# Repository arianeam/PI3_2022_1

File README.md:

# PI3_2022_1: Vaso Inteligente

## Estrutura das pastas do projeto:

* app: Nesta pasta está disponível para download o aplicativo de celular.
* banco_de_dados: nesta pasta está disponível o arquivo JSON do Firebase Realtime Database utilizado, que pode ser importado para visualização e uso no Realtime Database.
* firmware: disponível o firmware para esp32 do projeto.
* hardware: disponível o projeto desenvolvido no kicad para a placa.
* imagens PI3: imagens utilizadas nas animações do display, a imagem do mascote do aplicativo, imagens utilizadas nesta documentação, e imagens utilizadas nos testes do display.

# Objetivo
O objetivo deste projeto é implementar um vaso inteligente baseado em Internet das Coisas, que irá monitorar os parâmetros de umidade do solo, luminosidade e temperatura de uma planta, e a partir destes parâmetros avaliar o estado da planta, com base em um banco de dados que contenha informações de espécies de plantas, ou dados personalizados pelo usuário. Detectando o estado da planta, será gerada uma expressão facial em um display contido no vaso, que representará esse estado, como por exemplo, em caso de falta de água para a planta, o vaso exibiria uma expressão de sede. O usuário poderá selecionar configurar os parâmetros da planta através do aplicativo de celular. Essa configuração poderá ser manual ou automática (selecionando a espécie de planta no aplicativo). 

# Serão monitorados os seguintes itens no vaso/planta:

* Temperatura;
* Umidade do solo;
* Luminosidade

## Luminosidade

A luminosidade será monitorada por faixas, que facilitará a logica para definir o estado da planta e a compreensão por parte do usuário.
Conforme o site "Paisagismo Bauru" em sua postagem ["Dicas de luminosidade para seu jardim", link 4](http://www.paisagismobauru.com.br/curiosidades/curiosidades/), a medição de luminosidade será dividida em três faixas:
* **Sol**:
O dia inteiro com iluminação solar direta. Luminosidade acima de 20.000 lux.

* **Meia Sombra**:
Variando de iluminação de poucas horas na parte da manhã e mais algumas poucas horas de iluminação na parte da tarde. Luminosidade variando de 5.000 a 20.000 lux.

* **Sombra**:
Iluminação indireta. Luminosidade de 2.500 a 5.000 lux.

## Umidade do solo

A umidade do solo também será definida com base em três faixas.
* **Seco**
* **Úmido**
* **Molhado**

# Desenvolvimento

## Sensores

Todos sensores, o display oled, e um dos ESP32 utilizados para o desenvolvimento do PI3, não foram comprados. Ambos integrantes da dupla já possuiam o material em casa. Foi efetuada a compra de mais um ESP32 para um dos integrantes da dupla. E o microprocessador utilizado na placa desenvolvida foi removido de um dos ESP32. Poderiam ter sido utilizados outros sensores de melhor desempenho, porém optou-se por manter o menor custo possível nesta primeira versão do Vaso Inteligente.

A comunicação entre o hardware e o banco de dados utilizado ocorre por meio de Wi-Fi, pois o microprocessador utilizado (ESP32-WROOM-32) possui antena integrada.

**OBS.: Os sensores que utilizam os canais de ADC passam pelo circuito de entradas analógicas antes de chegar aos canais ADC, passando pelos buffers que irão proteger as entradas ADC**

### DHT11: sensor de temperatura e umidade

Datasheet: https://www.mouser.com/datasheet/2/758/DHT11-Technical-Data-Sheet-Translated-Version-1143054.pdf

[O elemento sensor de temperatura é um termistor do tipo NTC e o sensor de Umidade é do modelo HR202, o circuito interno faz a leitura dos sensores e se comunica a um microcontrolador, através de um sinal serial de uma via.](https://www.filipeflop.com/produto/modulo-sensor-de-umidade-e-temperatura-dht11-ky-015/)
O DHT11 foi alimentado com o 3v3 e o GND do ESP32, e o pino de dados foi ligado ao pino D27 do microcontrolador.

## LDR 5mm

Datasheet: https://www.filipeflop.com/img/files/download/Datasheet_LDR.pdf

[O Sensor de Luminosidade LDR (Light Dependent Resistor) é um componente cuja resistência varia de acordo com a intensidade da luz. Quanto mais luz incidir sobre o componente, menor a resistência.](https://www.filipeflop.com/produto/sensor-de-luminosidade-ldr-5mm/). Foi utilizado o canal 5 do ADC1 do ESP32 para receber a tensão do LDR, que em seguida, passa por uma função de leitura do firmware.

Foi necessário realizar a linearização dos valores do LDR para que ele atendesse as faixas de luminosidade exigidas pelo projeto. O método utilizado para realizar a linearização está descrito no seguinte link: https://www.digikey.com/en/maker/projects/design-a-luxmeter-with-an-ldr-and-an-arduino/623aeee0f93e427bb57e02c4592567d1

Passos seguidos para a linearização:

* Um multímetro foi conectado no LDR para monitorar a resistência;
* O luxímetro comercial foi posicionado ao lado do LDR, de forma que a incidência de luz seja a mesma em ambos;
* Em uma planilha foi registrada a resistência do LDR medida pelo multímetro e o valor aferido pelo luxímetro comercial;
* O passo anterior foi repetido para outros níveis de luminosidade, de forma que para cada medida da resistência do LDR houvesse uma medida do luxímetro;
* A partir dos dados registrados na planilha foi gerado um gráfico que pode ser ajustado com base na equação y = m.b. Foi utilizada a expressão fornecida no link informado anteriormente, linearizando o gráfico;

Assim é possível construir a função para leitura do LDR e ajustar os coeficientes.

## Higrômetro HL-69 (YL-69)

Guia (datasheet não encontrado): https://usermanual.wiki/Pdf/instructions.261306374.pdf

[Este Sensor de Umidade do Solo Higrômetro foi feito para detectar as variações de umidade no solo. Ele funciona da seguinte forma: quando o solo está seco, a saída do sensor fica em estado alto e quando úmido, a saída do sensor fica em estado baixo. O limite entre seco e úmido pode ser ajustado através do potenciômetro presente no sensor que regulará a saída digital D0. Contudo, para ter uma resolução melhor, é possível utilizar a saída analógica A0 e conectar a um conversor AD.](https://www.filipeflop.com/produto/sensor-de-umidade-do-solo-higrometro/). Para este projeto foi utilizada a saída analógica A0. O canal 4 do ADC1 do ESP32 é o responsável por receber o valor analógico do higrômetro. A alimentação do sensor foi feita através do 3v3 e GND do ESP32.

## Bateria

Abaixo imagem do circuito do carregador da bateria e função de leitura no firmware. Para medir a tensão da bateria proveniente do circuito do carregador foi utilizado o canal 6 do ADC1 do ESP32.

## Display oled SSD1306 128x64

O display utilizado foi o oled SSD1306 de 128x64. As animações para o display foram desenhadas no software Inkscape, com a área de 128x64px, exportadas para PNG, e em seguida convertida para outra extensão bitmap, a extensão XBM, respeitando a função da biblioteca para display SSD1306 utilizada no firmware, ssd1306_load_xbm. É importante observar quais formatos as funções aceitam quando utilizar bibliotecas de terceiros, caso contrário a imagem será exibida no display de forma distorcida, devido a forma como os bits são dispostos em cada tipo de extensão bitmap. Uma melhoria interessante para a estética do projeto é utilizar um display maior e com uma melhor resolução. Como um dos integrantes da dupla já possuia o display SSD1306, optou-se por usá-lo no projeto, reduzindo os custos do protótipo.

## Pinos utilizados do microprocessador ESP32-WROOM-32

## Firmware

O desenvolvimento ocorreu no microcontrolador ESP32-WROOM-32, da Espressif, utilizando o  framework oficial da Espressif, o ESP-IDF, que é voltado para o desenvolvimento de aplicações parar toda a família ESP32. Foi utilizada a extensão ESP-IDF no editor de códigos Visual Studio Code. 
A linguagem de programação utilizada no firmware foi C++/C. Os componentes do framework ESP-IDF são disponibilizados em C, porém, devido o uso de uma biblioteca em C++, necessária para comunicação com o banco de dados.

* **Github Espressif**: https://github.com/espressif

* **Github Espressif ESP-IDF**: https://github.com/espressif/esp-idf

* **Biblioteca utilizada para o DHT11**: https://github.com/UncleRus/esp-idf-lib/tree/master/components

* **Biblioteca utilizada para o Google Firebase Realtime Database**: https://github.com/dahmadjid/Firebase-idf 

## Armazenamento de dados e aplicativo de celular
Para armazenar os dados do aplicativo e dados lidos dos sensores do ESP32, e agilizar a comunicação com o aplicativo foi utilizada a ferramenta do Google Firebase.
O Firebase é uma plataforma para agilizar a criação e engajamento de aplicativos. Foi criado um projeto no Google Firebase, no qual foi vinculado o aplicativo de celular criado para o Vaso Inteligente. E para armazenar os dados e sincronizar em tempo real, tanto com o aplicativo quanto com o ESP32, foi utilizada a ferramenta Firebase Realtime Database. O Firebase Realtime Database é um banco de dados NoSQL hospedado na nuvem. Com ele, você armazena e sincroniza dados JSON entre os usuários em tempo real.
O aplicativo foi desenvolvido na plataforma Kodular, através de blocos lógicos de programação. Com o link do Realtime Database e a chave de API fornecida na criação do projeto no Firebase, além de algumas configurações de regras, é fácil realizar a comunicação com o aplicativo que foi desenvolvido no Kodular. E para o ESP32 se comunicar com o Firebase também foi utilizado o link do banco de dados e a chave API, aplicados na biblioteca utilizada, disponível no seguinte github: https://github.com/dahmadjid/Firebase-idf.

## Hardware

O esquemático e roteamento da placa foi realizado no software Kicad. A placa foi desenvolvida com face dupla, e a transferência foi realizada com o método "transferência fotográfica de imagem". Para saber mais sobre o método acesse os seguintes links:
* https://tec-ci.com.br/blog/circuito-impresso/transferencia-fotografica-de-imagem-trilhas-circuito-impresso/

* https://portal.vidadesilicio.com.br/confeccionando-de-placas-de-circuito-impresso-com-tinta-fotossensivel/

### Esquemático: https://github.com/arianeam/PI3_2022_1/blob/bc9ce70044babedad0d30e4cae6119c7fe134467/imagens%20PI3/hardware.pdf

### Placa:

#### 3D:

#### Confecção:

# Considerações

* Só foi utilizado o LDR como sensor de luminosidade neste projeto devido baixo custo, porém em larga escala é inviável pois é necessário linearizar um a um os LDRs, já que não serão construtivamente idênticos.
* Os DHT11 utilizados por vezes tiveram erro maior que +-2°C, e eles não estava medindo a umidade corretamente (por exemplo, deveriam medir 90% e estavam apresentando 40% de umidade relativa do ar). Portanto talvez utilizar um LM35 ou DHT22 seria uma melhor alternativa. O DHT11 foi utilizado pois já estava disponível, reduzindo custos de protótipo.
* Se possível, utilizar um display maior, para melhor experiência do usuário.
* Foi utilizado o Firebase Realtime Database, dentro dos limites de gratuidade, pela facilidade de uso para a prototipagem, mas pode-se optar por outros bancos e servidores além do Google, como por exemplo o AWS, ou Azure (ou optar por pagar o plano da Google para utilizar todas ferramentas disponíves).

# Pesquisa bibliográfica

Os links a seguir referem-se a pesquisa sobre os parâmetros de umidade, temperatura e luminosidade para os cuidados com diferentes espécies de plantas. 
Esses parâmetros foram utilizados para entender quais parâmetros medir e como trabalhá-los no firmware e app.

1. https://feelingsandflowers.com/cactus-care-guide-watering

2. https://www.colibriorquideas.com.br/pagina-Dicas_de_Cultivo

3. https://www.cpt.com.br/artigos/orquideas-luminosidade#:~:text=Para%20a%20maioria%20das%20orquídeas,fotômetro%20de%20uma%20máquina%20fotográfica.

4. http://www.paisagismobauru.com.br/curiosidades/curiosidades/

5. http://paisagismobauru.com.br/data/documents/CatalogoPlantasOrnamentais.pdf

6. https://www.cultivando.com.br/sol-pleno-meia-sombra-sombra-entenda-a-diferenca-para-as-plantas/#:~:text=Em%20uma%20sala%20muito%20bem,100%20lux%2C%20ou%2050.000%20lux!

7. https://www.gabrielkehdi.com/single-post/plantas-para-sombra

8. https://www.tecnologiaetreinamento.com.br/jardim/floricultura-jardim/cultivo-de-orquideas-substrato-clima-e-luminosidade

9. https://www.floresefolhagens.com.br/plantas-por-categorias/

10. https://www.cpt.com.br/artigos/orquideas-luminosidade#:~:text=Para%20a%20maioria%20das%20orquídeas,fotômetro%20de%20uma%20máquina%20fotográfica. 

11. https://plantasemcasa.com.br/plantas-de-meia-sombra-para-vasos/

12. https://casa.abril.com.br/jardins-e-hortas/tudo-que-voce-precisa-saber-sobre-iluminacao-plantas-internas/

13. https://casa.abril.com.br/jardins-e-hortas/6-dicas-regar-plantas/

14. https://comozed.com/quantos-lumens-são-necessários-para-cultivar-plantas

15. https://www.youtube.com/watch?v=gclYWybQeI4

16. https://www.emporioluz.com.br/blog/a-influencia-da-luz-nas-plantas/

17. https://greenpower.net.br/blog/iluminacao-tamanho-do-grow/

18. https://wchristianeletrotecnica.wordpress.com/2013/01/23/a-luz-e-as-plantas/

19. https://www.gazetadopovo.com.br/haus/paisagismo-jardinagem/voce-sabe-como-regar-corretamente-suas-plantas/

20. https://revistacasaejardim.globo.com/Casa-e-Jardim/Paisagismo/Plantas/noticia/2021/09/plantas-de-sol-11-especies-resistentes-e-que-demandam-luz-direta.html

21. https://cantinhodovideo.com/10-tipos-de-plantas-para-plantar-em-sol-pleno/

22. https://luxafrica.life/2021/02/5-tipos-de-plantas-para-ter-em-casa/

23. https://www.youtube.com/watch?v=qcFD-a5sp2o

24. https://www.youtube.com/watch?v=mpvMj9PM-7I

25. https://www.temarquitetura.com.br/single-post/2015/01/30/Plantas-X-sol

26. https://casa.umcomo.com.br/artigo/plantas-resistentes-ao-sol-e-ao-frio-29387.html

27. https://www.tgservices.com.br/efeito-da-temperatura-sobre-as-plantas/

28. https://100fronteiras.com/brasil/noticia/plantas-para-cultivar-ambientes-meia-sombra-sombra-total/

29. https://www.planejpb.com.br/post/jardinagem

30. https://www.casadevalentina.com.br/blog/papo-de-paisagista-plantas-para-sombra/

31. https://www.metodopaisagismo.com.br/single-post/2017/01/03/sol-sombra-ou-meia-sombra

32. https://portalvidalivre.com/articles/148

33. https://minhasplantas.com.br/tv/dentro-de-casa/descubra-quanto-de-luz-sua-planta-precisa/

34. https://www.jardinet.com.br/2019/04/sol-pleno-meia-sombra-luz-direta-ou.html

35. https://www.scielo.br/j/aa/a/4qHVqmHknnPWmwHx3KmMkrB/?lang=pt

36. https://www.atelierecul.com/single-post/2018/02/27/tipos-de-rega-e-luminosidade-em-plantas

37. https://cactosesuculentas.com/suculentas/qual-a-melhor-iluminacao-para-as-suculentas/

38. https://www.editorarealize.com.br/editora/anais/conimas-e-conidis/2019/TRABALHO_EV133_MD4_SA37_ID1471_01112019113159.pdf

39. https://viverorquideaseideias.blogspot.com/2017/02/como-definir-rega-para-suas-plantas.html

40. https://exame.com/casual/os-6-erros-mais-comuns-ao-cuidar-de-plantas-e-como-evita-los/

41. https://eos.com/pt/blog/umidade-do-solo/

42. https://www.vaisala.com/sites/default/files/documents/CEN-BAU-Greenhouse-Climate-Application-Note-B211142PT-A.pdf

43. https://greenpower.net.br/blog/cultivo-indoor-controle-de-temperatura/

44. https://www.orquideasnoape.com.br/2021/02/suculenta-echeveria-lilacina.html

# Plantas que foram inseridas no banco de dados:
## lírio da paz

https://guiadejardinagem.com.br/plantas-para-dentro-de-casa/#O_que_sao_Plantas_de_Interior

https://portalvidalivre.com/articles/96

https://casa.abril.com.br/jardins-e-hortas/como-cultivar-lirio-da-paz/

https://blog.plantei.com.br/lirio-da-paz/

https://vivercomplantas.wordpress.com/2018/01/30/lirio-da-paz-para-locais-sombreados-meia-sombra/

# planta-jade

https://www.jardineiro.net/plantas/planta-jade-crassula-ovata.html
https://portalvidalivre.com/articles/44
https://guiadassuculentas.com/suculenta-jade-saiba-tudo-sobre-essa-planta/
https://www.picturethisai.com/pt/care/Crassula_ovata.html#:~:text=Forneça%20temperatura%20adequada%20(%2025%20℃,luz%20(luz%20difusa%20brilhante).
https://www.noticiasdejardim.com/plantas-de-interior/crassula-ovata-arvore-de-jade-uma-especie-muito-facil-de-cultivar/

# planta fantasma 

https://www.floresefolhagens.com.br/planta-fantasma-graptopetalum/

https://portalvidalivre.com/articles/143

https://www.picturethisai.com/pt/care/Graptopetalum_paraguayense.html

https://cibercactus.com/pt/graptopetalum-paraguayense/

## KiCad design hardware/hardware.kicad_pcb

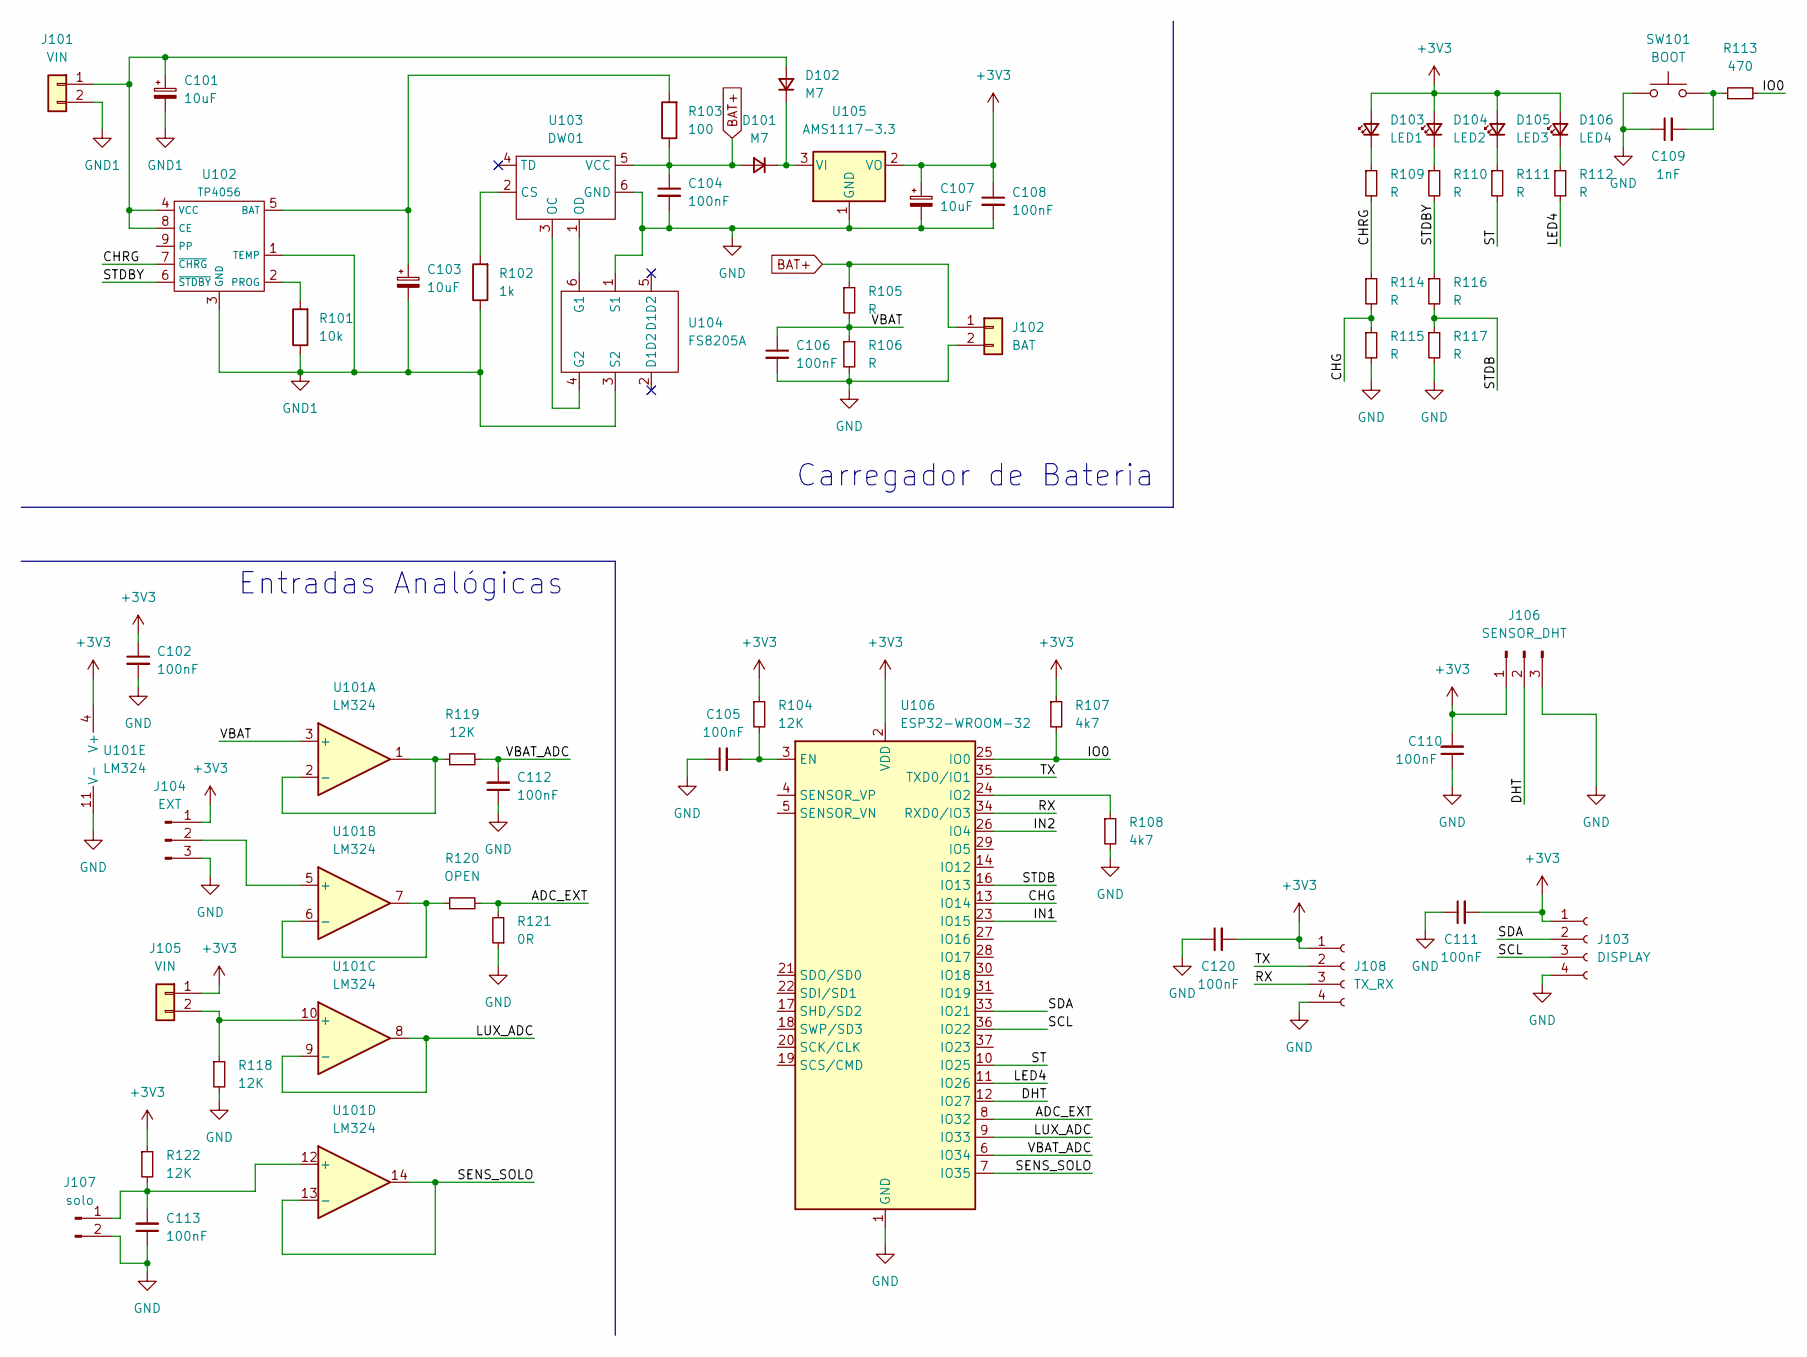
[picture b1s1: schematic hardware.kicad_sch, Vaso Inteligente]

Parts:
C101, C103, C107: 10uF; CP_Elec_5x3
C102, C104, C105, C106, C108, C110, C111, C112, C113, C120: 100nF; C_0805_2012Metric_Pad1.18x1.45mm_HandSolder
C109: 1nF; C_0805_2012Metric_Pad1.18x1.45mm_HandSolder
D101, D102: M7; D_MiniMELF_Handsoldering
D103: LED1; LED_0805_2012Metric_Pad1.15x1.40mm_HandSolder
D104: LED2; LED_0805_2012Metric_Pad1.15x1.40mm_HandSolder
D105: LED3; LED_0805_2012Metric_Pad1.15x1.40mm_HandSolder
D106: LED4; LED_0805_2012Metric_Pad1.15x1.40mm_HandSolder
J101, J105: VIN; PinHeader_1x02_P2.54mm_Vertical
J102: BAT; PinHeader_1x02_P2.54mm_Vertical
J103: DISPLAY; PinSocket_1x04_P2.54mm_Vertical
J104: EXT; PinHeader_1x03_P2.54mm_Vertical
J106: SENSOR_DHT; PinHeader_1x03_P2.54mm_Vertical
J107: solo; PinHeader_1x02_P2.54mm_Vertical
J108: TX_RX; PinSocket_1x04_P2.54mm_Vertical
R101: 10k; R_0805_2012Metric_Pad1.20x1.40mm_HandSolder
R102: 1k; R_0805_2012Metric_Pad1.20x1.40mm_HandSolder
R103: 100; R_0805_2012Metric_Pad1.20x1.40mm_HandSolder
R104, R118, R119, R122: 12K; R_0805_2012Metric_Pad1.20x1.40mm_HandSolder
R105, R106, R109, R110, R111, R112, R114, R115, R116, R117: R; R_0805_2012Metric_Pad1.20x1.40mm_HandSolder
R107, R108: 4k7; R_0805_2012Metric_Pad1.20x1.40mm_HandSolder
R113: 470; R_0805_2012Metric_Pad1.20x1.40mm_HandSolder
R120: OPEN; R_0805_2012Metric_Pad1.20x1.40mm_HandSolder
R121: 0R; R_0805_2012Metric_Pad1.20x1.40mm_HandSolder
SW101: BOOT; SW_SPST_CK_RS282G05A3
U101: LM324; SOIC-14_3.9x8.7mm_P1.27mm
U102: TP4056; SOIC-8-1EP_3.9x4.9mm_P1.27mm_EP2.29x3mm
U103: DW01; SOT-23-6_Handsoldering
U104: FS8205A; SOT-23-6_Handsoldering
U105: AMS1117-3.3; SOT-223-3_TabPin2
U106: ESP32-WROOM-32

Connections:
+3V3: C102.1, C107.1, C108.1, C110.2, C111.2, C120.2, D103.2 (A), D104.2 (A), D105.2 (A), D106.2 (A), J103.1, J104.1, J105.1, J106.1, J108.1, R104.1, R107.1, R122.1, U101.4 (V+), U105.2 (VO), U106.2 (VDD)
/ADC_EXT: R120.2, R121.2, U106.8 (IO32)
/CHG: R114.2, R115.1, U106.13 (IO14)
/CHRG: R109.2, R114.1, U102.7 (~CHRG)
/DHT: J106.2, U106.12 (IO27)
/IN1: U106.23 (IO15)
/IN2: U106.26 (IO4)
/IO0: R107.2, R113.2, U106.25 (IO0)
/LED4: R112.2, U106.11 (IO26)
/LUX_ADC: U101.8, U101.9 (-), U106.9 (IO33)
/RX: J108.3, U106.34 (RXD0/IO3)
/SCL: J103.3, U106.36 (IO22)
/SDA: J103.2, U106.33 (IO21)
/SENS_SOLO: U101.13 (-), U101.14, U106.7 (IO35)
/ST: R111.2, U106.10 (IO25)
/STDB: R116.2, R117.1, U106.16 (IO13)
/STDBY: R110.2, R116.1, U102.6 (~STDBY)
/TX: J108.2, U106.35 (TXD0/IO1)
/VBAT: C106.1, R105.2, R106.1, U101.3 (+)
/VBAT_ADC: C112.2, R119.2, U106.6 (IO34)
BAT+: C104.1, D101.2 (A), J102.1, R103.1, R105.1, U103.5 (VCC)
GND: C102.2, C104.2, C105.1, C106.2, C107.2, C108.2, C109.1, C110.1, C111.1, C112.1, C113.1, C120.1, J102.2, J103.4, J104.3, J106.3, J107.2, J108.4, R106.2, R108.2, R115.2, R117.2, R118.2, R121.1, SW101.1, U101.11 (V-), U103.6 (GND), U104.1 (S1), U105.1 (GND), U106.1 (GND), U106.15 (GND), U106.38 (GND), U106.39 (GND)
GND1: C101.2, C103.2, J101.2, R101.1, R102.1, U102.1 (TEMP), U102.3 (GND), U104.3 (S2)
unnamed: C103.1, R103.2, U102.5 (BAT)
unnamed: C105.2, R104.2, U106.3 (EN)
unnamed: C109.2, R113.1, SW101.2
unnamed: C113.2, J107.1, R122.2, U101.12 (+)
unnamed: D101.1 (K), D102.1 (K), U105.3 (VI)
unnamed: D103.1 (K), R109.1
unnamed: D104.1 (K), R110.1
unnamed: D105.1 (K), R111.1
unnamed: D106.1 (K), R112.1
unnamed: J104.2, U101.5 (+)
unnamed: J105.2, R118.1, U101.10 (+)
unnamed: R101.2, U102.2 (PROG)
unnamed: R102.2, U103.2 (CS)
unnamed: R108.1, U106.24 (IO2)
unnamed: R119.1, U101.1, U101.2 (-)
unnamed: R120.1, U101.6 (-), U101.7
unnamed: U103.1 (OD), U104.6 (G1)
unnamed: U103.3 (OC), U104.4 (G2)

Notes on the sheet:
Carregador de Bateria
Entradas Analógicas

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
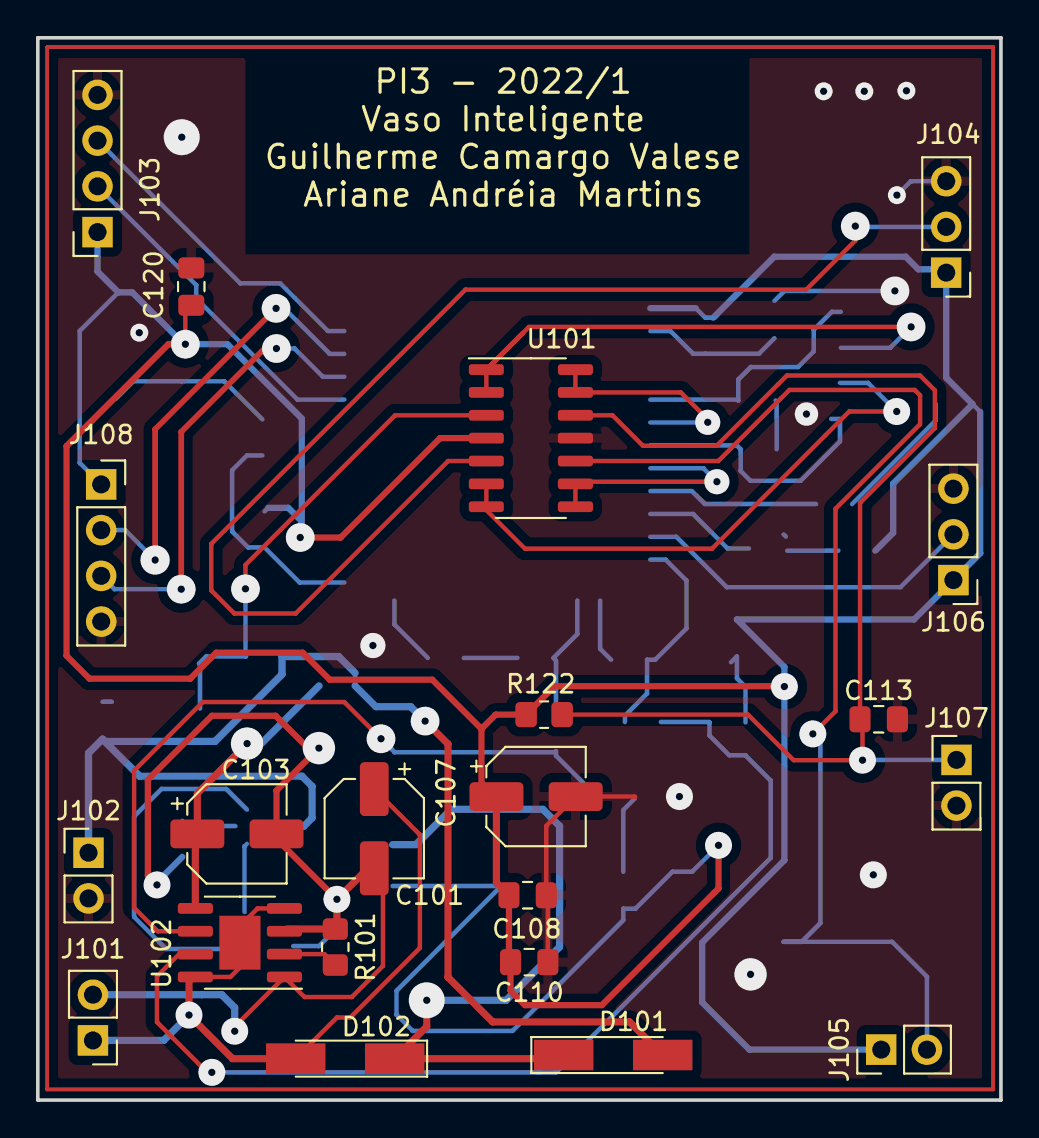
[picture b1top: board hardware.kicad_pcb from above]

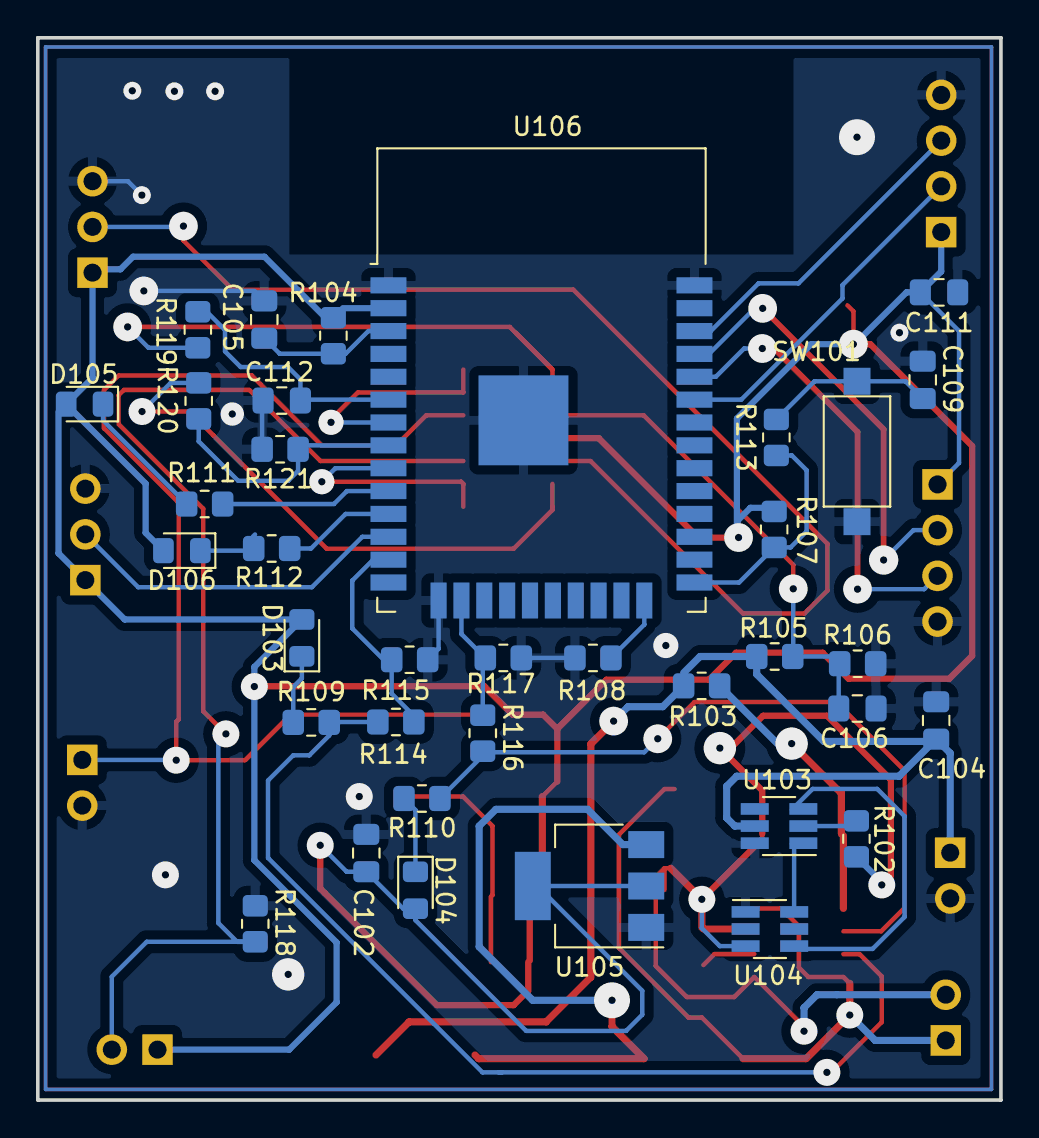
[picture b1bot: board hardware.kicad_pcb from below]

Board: 2 copper layers, 53.5 x 59.0 mm, 57 parts (36 on the bottom side), 40 nets.

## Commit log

2022-04-15 Update README.md
    descrição pi3
2022-04-19 Rename Diagrama_blocos.md to README.md
2022-04-25 Create classes_plantas.db
    - pasta que contém o banco de dados com os parâmetros de umidade, temperatura, e luz para espécies de plantas
2022-05-01 Código DHT11
    bug: Não consegui gravar o código na placa ESP32. pesquisei sobre o problema e tentei as soluções porém não resolveu
2022-05-02 teste do sensor DHT11
    Realizado teste do sensor DHT11 com a placa arduino uno
2022-05-02 teste sensor DHT11
    Consegui gravar na esp32 (não estava conseguindo gravar em um teste anterior)
    Realizado teste do DHT11 agora com a esp32
2022-05-03 ESP32 e DHT11
    Diagrama da ligação utilizado no teste do sensor DHT11 (temperatura e umidade) com o micro controlador ESP32
2022-05-04 teste ldr
2022-05-16 diretório teste DHT11 ESP_IDF
2022-05-16 delet project
2022-05-16 teste projeto esp-idf
    bug: -- Configuring incomplete, errors occurred!
    See also "C:/Users/Ari/Documents/GitHub/PI3_2022_1/sensores/SENSORES_ESP_IDF/build/CMakeFiles/CMakeOutput.log".
    ←[31mFAILED: ←[0mbuild.ninja
    C:\Users\Ari\.espressif\tools\cmake\3.20.3\bin\cmake.exe --regenerate-during-build -SC:\Users\Ari\Documents\GitHub\PI3_2022_1\sensores\SENSORES_ESP_IDF -BC:\Users\Ari\Documents\GitHub\PI3_2022_1\sens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
    ninja: error: rebuilding 'build.ninja': subcommand failed
    O processo de terminal "C:\Windows\System32\WindowsPowerShell\v1.0\powershell.exe -Command ninja " foi terminado com o
2022-05-17 teste esp-idf
    consegui compilar, mantive dentro da pasta components apenas as bibliotecas que utilizei no teste
2022-05-17 teste dht11 esp-idf
    consegui ler a umidade e temperatura
2022-05-18 dht11 com fila
    implementada uma fila para passar os parâmetros do dht11 para outra task. Foi criada uma task teste
2022-05-19 remoção de variável
    removi duas variáveis de temp e umidade que não estavam sendo usadas
2022-05-22 Atualizado gitignore
2022-05-26 Update main.c
    Inserida task para o adc para uso do sensor hl-69 (umidade solo).
2022-05-30 Adcionado display SSD1306
2022-06-01 Corrigido compilacao no esp32
2022-06-02 Removido as pastas vazias
2022-06-02 biblioteca para display OLED
2022-06-08 Update sdkconfig
    teste para arrumar erro das bibliotecas na compilação
2022-06-08 task display
    Criei uma tarefa para o display.
2022-06-09 removido código antigo
2022-06-09 imagem xbm
    correção do mapeamento da imagem para formato xbm para impressão no display
2022-06-09 animação teste emoticom
    testei a animação de alguns emotes que fiz
2022-06-15 Adicionado wifi
2022-06-20 firebase
    testes da biblioteca em c++ para o firebase
2022-06-23 Adicionado firebase
2022-06-23 classe display
    adaptei os arquivos display.c e .h para criar uma classe do display
2022-06-23 include biblioteca
    incluida a pasta esp-idf-lib em components para obter a biblioteca dht.
2022-06-23 correção classe display
2022-06-23 remoção de pasta driver de components
2022-06-24 classe dht11
    classe dht11 em andamento
2022-06-24 teste classe dht11
2022-06-27 dht11 classe
2022-06-27 tarefas
    -removida classe dht11 pois funcionou sem a classe
    - criados os arquivos tarefas.cpp e tarefas.h para separar a implementação das task do main
2022-06-27 Revert "Update firebase_config.h"
    This reverts commit 1c78fae960044455695d361d9d172ea45f16b423.
2022-06-27 v1
    - classe display
    - tarefa dht
2022-06-27 classe adc1
2022-06-27 classe adc1
    adc1 está lendo valor
2022-06-30 bd
    criei classe para banco de dados. comecei lendo o endereço mac da esp32, que será utilizado para identificação no banco de dados
2022-07-04 firebase
    função para criar estrutura no firebase conforme endereço mac da esp32
2022-07-04 identificação do dispositivo
2022-07-05 Update banco_de_dados.cpp
    testes bd
2022-07-09 adicionado sobrecarga no display
    Sobrecarga nas funções do display
2022-07-12 pastas
    -salvei o arquivo json do firebase e o .apk do aplicativo
2022-07-13 adicionado bateria
2022-07-13 testes adc
2022-07-13 hardware
2022-07-13 atualizado esquemático
2022-07-13 update bd
2022-07-13 update bd json
2022-07-14 pcb
    organizando componentes
2022-07-14 esq e pcb
2022-07-15 pcb update
2022-07-15 update pcb
2022-07-15 update sch
2022-07-15 pcb
    finalizado
    - precisa revisar pcb e esquemático
2022-07-16 save
2022-07-16 teste dht firebase
2022-07-16 teste
2022-07-16 sobrecarga de funções do banco de dados
2022-07-17 get data
2022-07-17 atualizado codigo
2022-07-17 adicionado função do luximetro
2022-07-17 update tasks
2022-07-17 update publish data
2022-07-18 Atualizado firmware
2022-07-18 imagens
2022-07-19 display emotes
2022-07-19 Create teste
2022-07-19 novos arquivos
2022-07-19 animações atualizadas
2022-07-20 gerado arquivos de fabricação
2022-07-20 error
2022-07-21 bd error
2022-07-22 alterado lógica de leitura do firebase
2022-07-22 update set temperatura sensor
2022-07-22 update testes
2022-07-22 update status
2022-07-23 Update main.cpp
    testes status ok
2022-07-27 atualizado pcb
